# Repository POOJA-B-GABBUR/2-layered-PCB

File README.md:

# 2-layered-PCB
simple 2-layered pcb

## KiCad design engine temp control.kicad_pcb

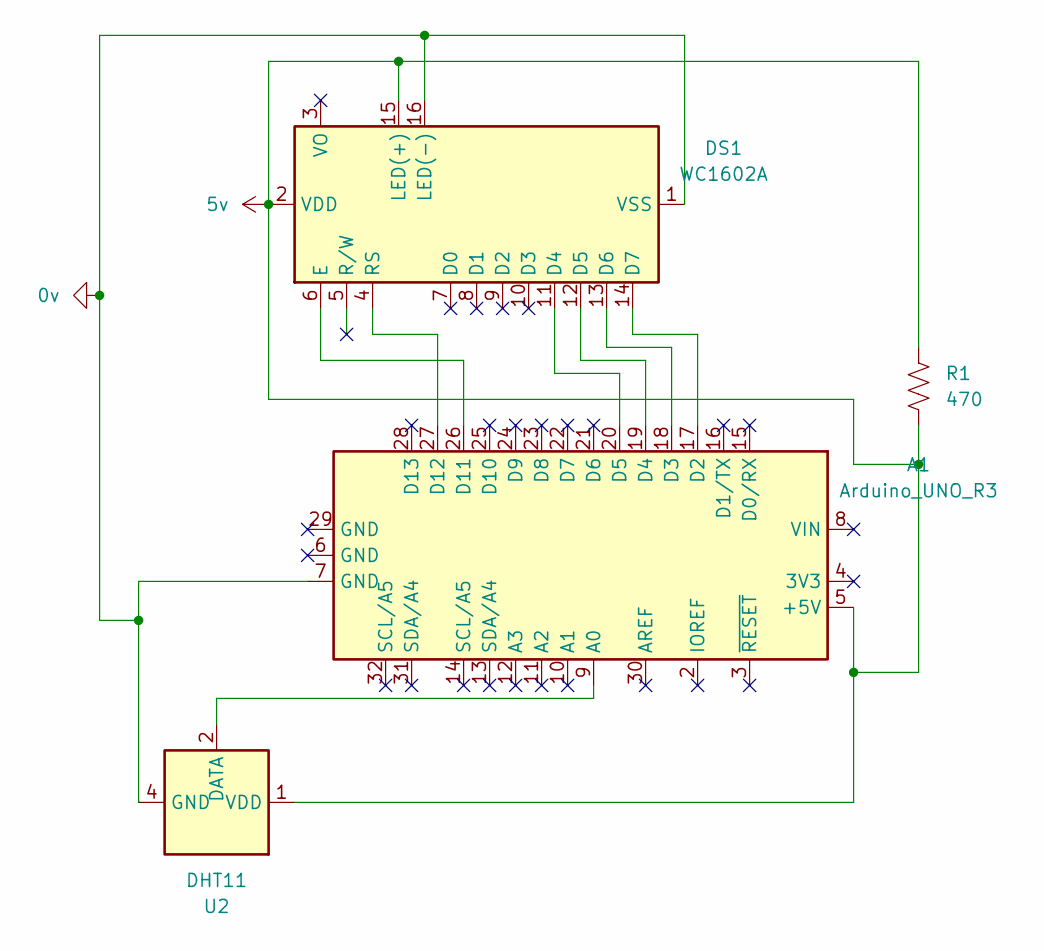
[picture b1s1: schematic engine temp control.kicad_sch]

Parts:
A1: Arduino_UNO_R3; Arduino_UNO_R3_WithMountingHoles
DS1: WC1602A
R1: 470; R_Axial_DIN0204_L3.6mm_D1.6mm_P5.08mm_Horizontal
U2: DHT11; Aosong_DHT11_5.5x12.0_P2.54mm

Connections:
0v: A1.7 (GND), DS1.1 (VSS), DS1.16 (LED(-)), U2.4 (GND)
5v: A1.5 (+5V), DS1.2 (VDD), DS1.15 (LED(+)), R1.1, R1.2, U2.1 (VDD)
unnamed: A1.9 (A0), U2.2 (DATA)
unnamed: A1.17 (D2), DS1.14 (D7)
unnamed: A1.18 (D3), DS1.13 (D6)
unnamed: A1.19 (D4), DS1.12 (D5)
unnamed: A1.20 (D5), DS1.11 (D4)
unnamed: A1.26 (D11), DS1.6 (E)
unnamed: A1.27 (D12), DS1.4 (RS)

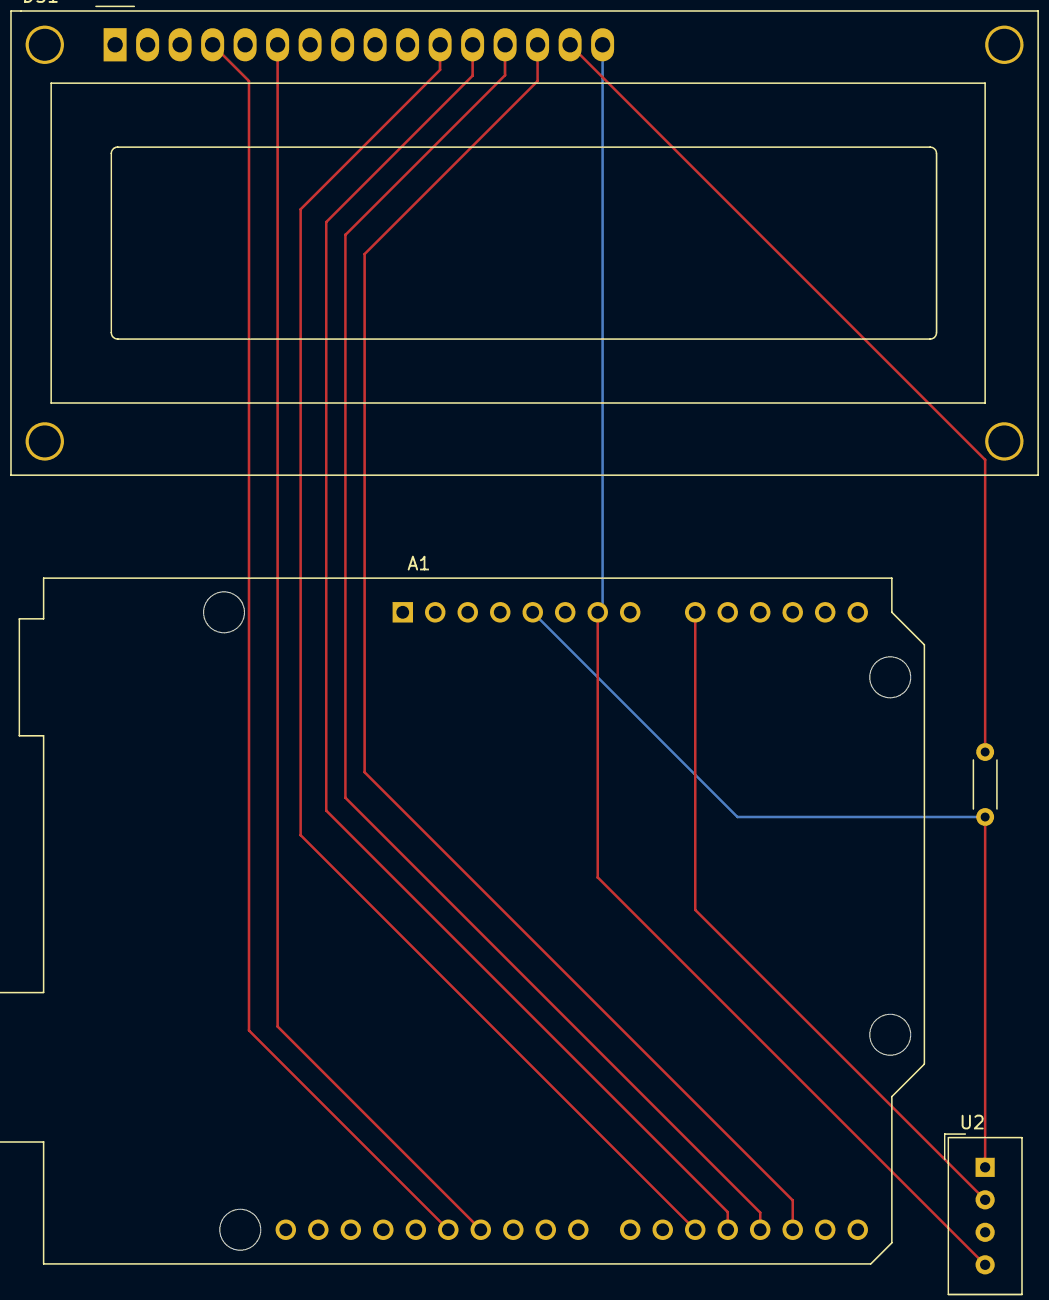
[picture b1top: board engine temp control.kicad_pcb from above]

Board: 2 copper layers, 4 parts (0 on the bottom side), 9 nets.

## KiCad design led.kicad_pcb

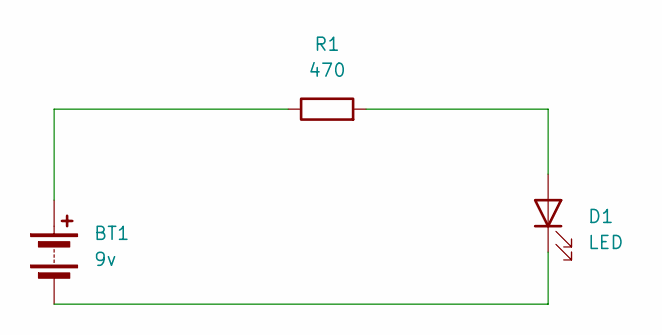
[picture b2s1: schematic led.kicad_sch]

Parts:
BT1: 9v; PinHeader_1x02_P2.54mm_Vertical
D1: LED; LED_0603_1608Metric_Pad1.05x0.95mm_HandSolder
R1: 470; R_0201_0603Metric

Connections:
unnamed: BT1.1 (+), R1.1
unnamed: BT1.2 (-), D1.1 (K)
unnamed: D1.2 (A), R1.2

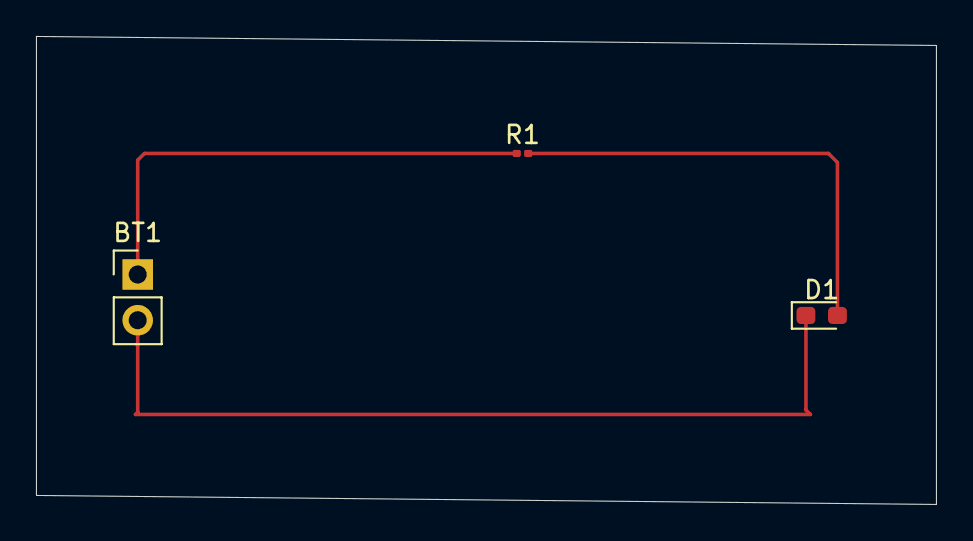
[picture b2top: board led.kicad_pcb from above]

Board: 2 copper layers, 50.0 x 26.0 mm, 3 parts (0 on the bottom side), 3 nets.
